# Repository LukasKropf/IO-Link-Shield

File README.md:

# IO-Link-Shield

Das IO-Link-Shield für Arduino wurde an der BFH  im Rahmen einer Projektarbeit erarbeitet. 
Dieses Repository enthällt alle wichtigen Daten zum Projekt. 

Die Dokumentation ist im Ordner Dokumente zu finden

[Bericht_io-Link Shield](https://github.com/LukasKropf/IO-Link-Shield/blob/master/Dokumente/Bericht_IO-Link%20Shield.pdf)

# Weiterführende Arbeiten:

Einige Zeit später wurde ein Nachfolgeprojekt gestartet in Rahmen einer Bachelorthesis.

[IO-Link Master Shield/Hat für Arduino und Raspberry Pi](https://bfh.easydocmaker.ch/search/abstract/2056/)

https://github.com/openiolink/io-link-master-shield-hat-sw

# Bilder

Hier einige Renderings:

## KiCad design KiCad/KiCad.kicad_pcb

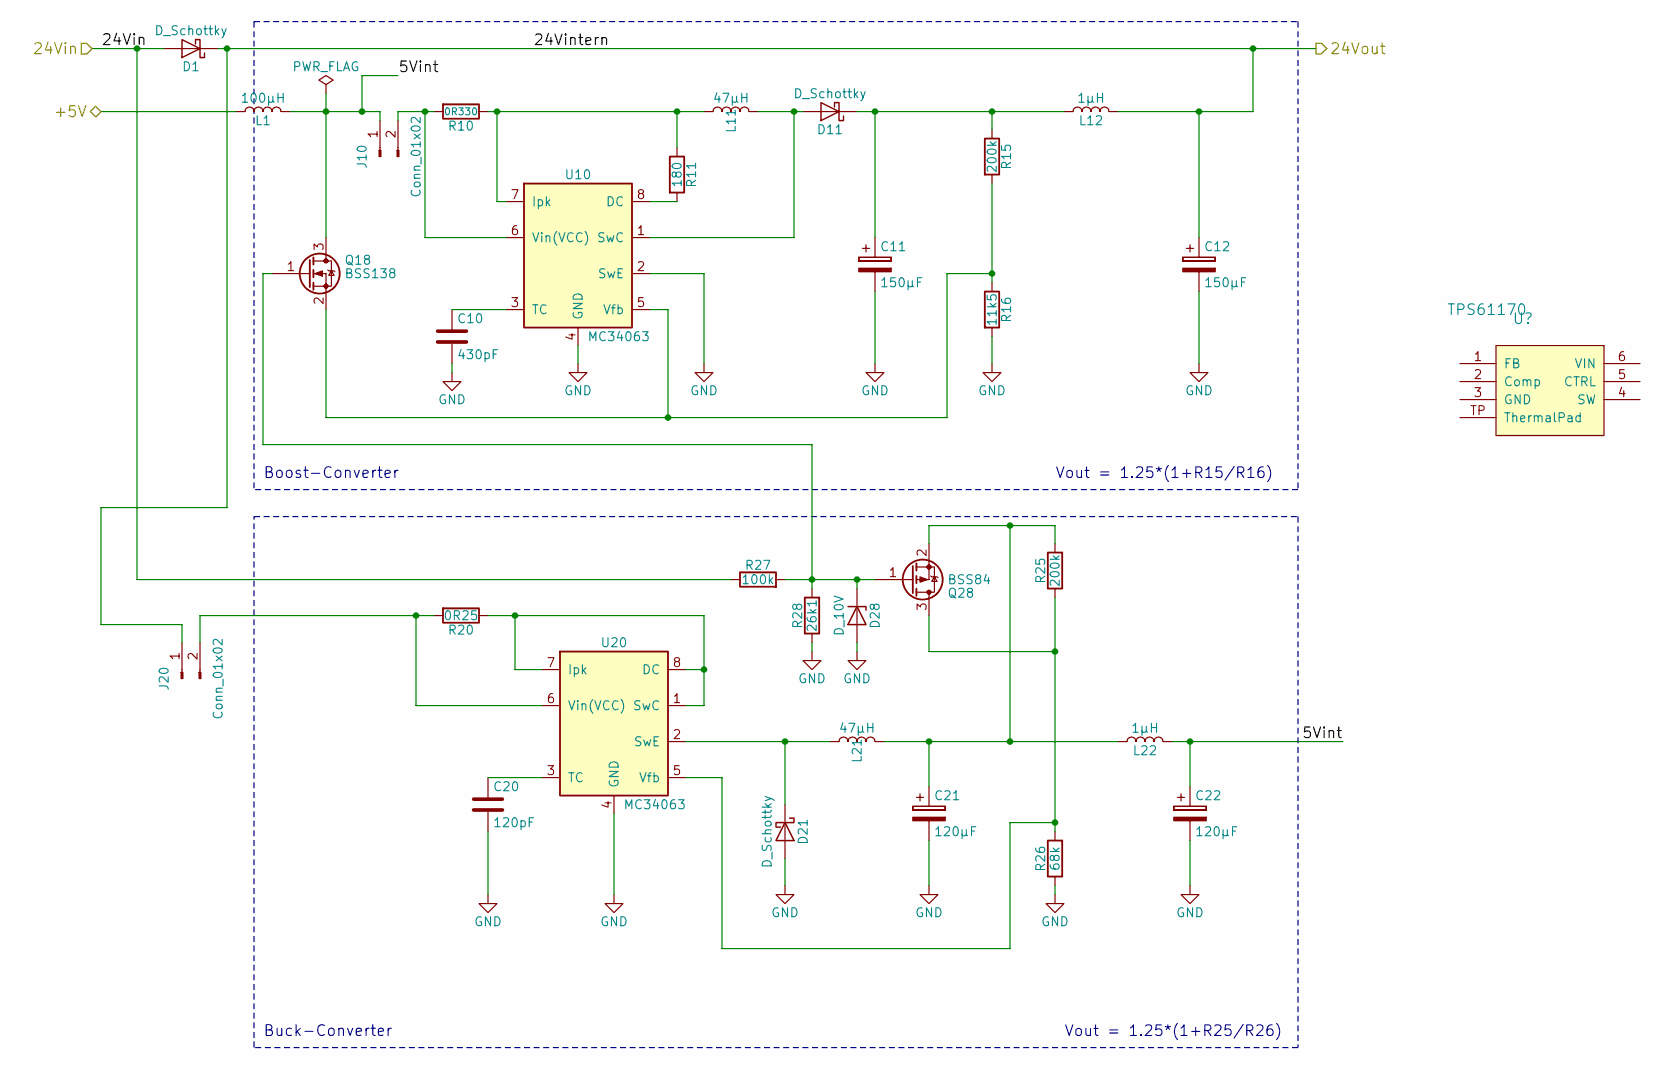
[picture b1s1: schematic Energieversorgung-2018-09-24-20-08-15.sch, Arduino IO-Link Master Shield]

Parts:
C10: 430pF; C_0805; part-num C0805C431J5GAC7800
C11, C12: 150µF; CP_Elec_8x10.5; part-num 35PEV150M8X10.5
C20: 120pF; C_0805; part-num GRM2165C1H121JA01D
C21, C22: 120µF; CP_Elec_6.3x5.7; part-num RSA1A121MCN1GS
D1, D11, D21: D_Schottky; D_SMF_DO-219; part-num SL04-HE3-08
D28: D_10V; D_SOD-123F; part-num NZH10C115
J10, J20: Conn_01x02; Pin_Header_Straight_1x02_Pitch2.54mm; part-num S1011EC-02-ND;SPC02SYAN
L1: 100µH; Murata_DG8040C; part-num 1267AY-101M=P3
L11, L21: 47µH; SRN6045; part-num SRN6045-470M
L12, L22: 1µH; L_0805; part-num LQM21FN1R0N00D
Q18: BSS138; SOT-23; part-num BSS138TA
Q28: BSS84; SOT-23; part-num BSS84-7-F
R10: 0R330; R_0805; part-num RL0805FR-7W0R33L
R11: 180; R_0805; part-num RC0805FR-07180RL
R15, R25: 200k; R_0805; part-num RC0805FR-07200KL
R16: 11k5; R_0805; part-num RC0805FR-0711K5L
R20: 0R25; R_0805; part-num RL0805FR-070R25L
R26: 68k; R_0805; part-num RC0805FR-0768KL
R27: 100k; R_0805; part-num RC0805FR-07100KL
R28: 26k1; R_0805; part-num RC0805FR-0726K1L
U10, U20: MC34063; SOIC-8-N; part-num MC34063ACD-TR

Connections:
/5V: L1.1; also elsewhere on the board
/24V: C12.1, D1.1 (K), J20.1, L12.2; also elsewhere on the board
/Energieversorgung/5Vint: C22.1, J10.1, L1.2, L22.2, Q18.3 (D)
/Energieversorgung/24Vin: D1.2 (A), R27.1; also elsewhere on the board
GND: C10.2, C11.2, C12.2, C20.2, C21.2, C22.2, D21.2 (A), D28.2 (A), R16.2, R26.1, R28.1, U10.2 (SwE), U10.4 (GND), U20.4 (GND); also elsewhere on the board
unnamed: C10.1, U10.3 (TC)
unnamed: C11.1, D11.1 (K), L12.1, R15.1
unnamed: C20.1, U20.3 (TC)
unnamed: C21.1, L21.2, L22.1, Q28.2 (S), R25.2
unnamed: D11.2 (A), L11.2, U10.1 (SwC)
unnamed: D21.1 (K), L21.1, U20.2 (SwE)
unnamed: D28.1 (K), Q18.1 (G), Q28.1 (G), R27.2, R28.2
unnamed: J10.2, R10.2, U10.6 (Vin(VCC))
unnamed: J20.2, R20.2, U20.6 (Vin(VCC))
unnamed: L11.1, R10.1, R11.1, U10.7 (Ipk)
unnamed: Q18.2 (S), R15.2, R16.1, U10.5 (Vfb)
unnamed: Q28.3 (D), R25.1, R26.2, U20.5 (Vfb)
unnamed: R11.2, U10.8 (DC)
unnamed: R20.1, U20.1 (SwC), U20.7 (Ipk), U20.8 (DC)

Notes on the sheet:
Boost-Converter
Buck-Converter
Vout = 1.25*(1+R15/R16)
Vout = 1.25*(1+R25/R26)

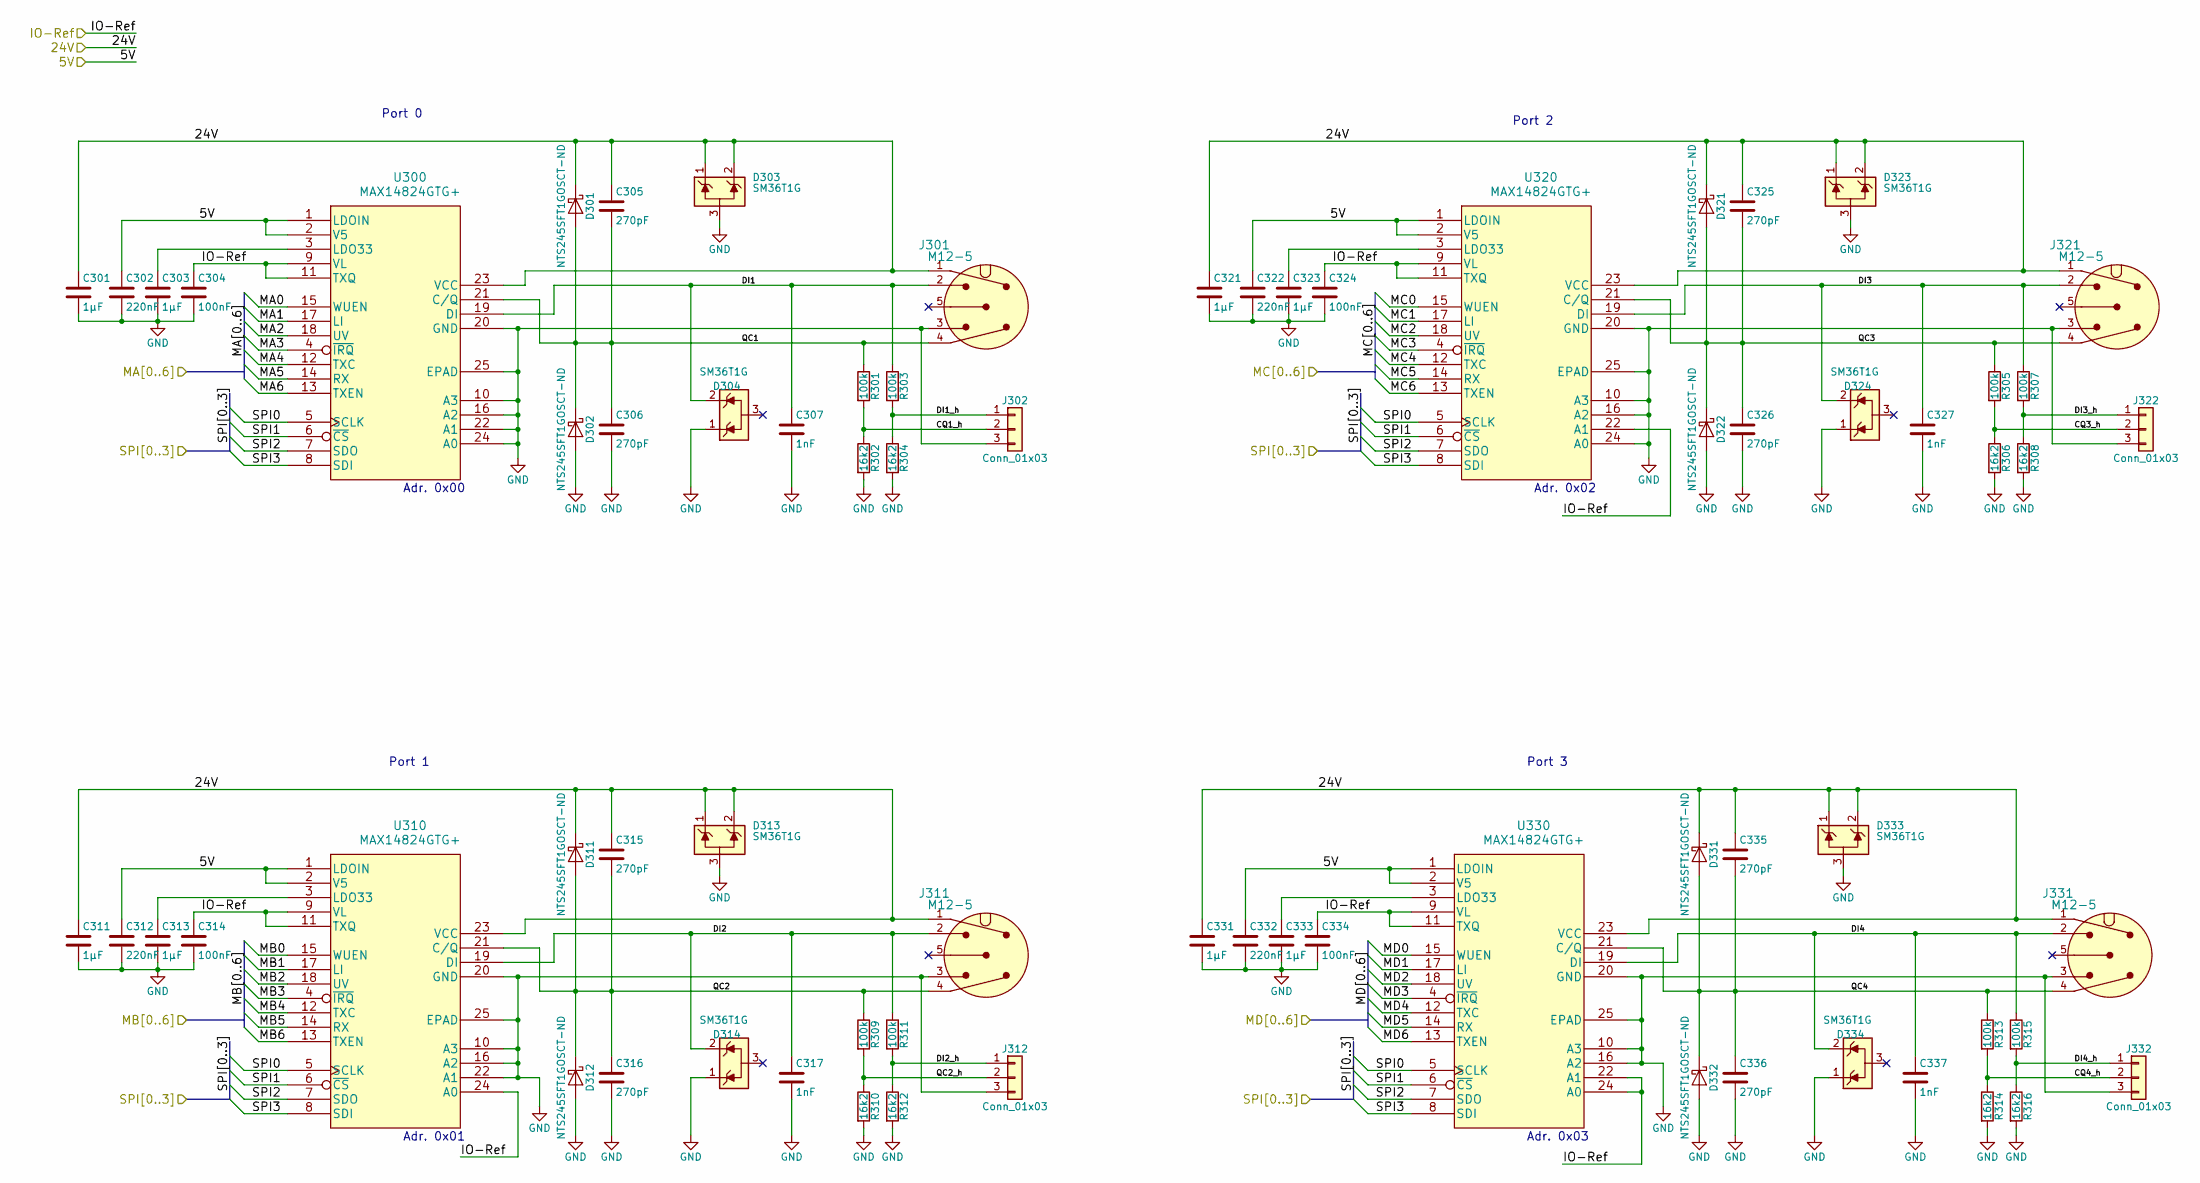
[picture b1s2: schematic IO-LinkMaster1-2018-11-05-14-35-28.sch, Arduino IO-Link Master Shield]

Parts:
C301, C311, C321, C331: 1µF; C_0805; part-num 885012207103
C302, C312, C322, C332: 220nF; C_0805; part-num 885012207018
C303, C313, C323, C333: 1µF; C_0805; part-num 885012207022
C304, C314, C324, C334: 100nF; C_0805; part-num 885012207016
C305, C306, C315, C316, C325, C326, C335, C336: 270pF; C_0805; part-num GRM2165C1H271JA01D
C307, C317, C327, C337: 1nF; C_0805; part-num GRM216R71H102KA01D
D301, D302, D311, D312, D321, D322, D331, D332: NTS245SFT1GOSCT-ND; D_SOD-123F; part-num NTS245SFT1GOSCT-ND
D303, D304, D313, D314, D323, D324, D333, D334: SM36T1G; SOT-23; part-num SM36T1G
J301, J311, J321, J331: M12-5; Phoenix_SACC-DSIV-M12FS-5CON-L180; part-num 1694237
J302, J312, J322, J332: Conn_01x03; Socket_Strip_Straight_1x03_Pitch2.54mm; part-num PPPC031LFBN-RC
R301, R303, R305, R307, R309, R311, R313, R315: 100k; R_0805; part-num RC0805FR-07100KL
R302, R304, R306, R308, R310, R312, R314, R316: 16k2; R_0805; part-num RC0805FR-0716K2L
U300, U310, U320, U330: MAX14824GTG+; QFN-24-1EP_4x4mm_Pitch0.5mm_Maxim; part-num MAX14824GTG+

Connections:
/0(Rx0): U300.14 (RX); also elsewhere on the board
/1(Tx0): U300.12 (TXC); also elsewhere on the board
/2(**): U330.4 (~IRQ); also elsewhere on the board
/3(**): U320.4 (~IRQ); also elsewhere on the board
/4(**): U310.4 (~IRQ); also elsewhere on the board
/5(**): U300.4 (~IRQ); also elsewhere on the board
/5V: C302.1, C312.1, C322.1, C332.1, U300.1 (LDOIN), U300.2 (V5), U310.1 (LDOIN), U310.2 (V5), U320.1 (LDOIN), U320.2 (V5), U330.1 (LDOIN), U330.2 (V5); also elsewhere on the board
/6(**): U300.13 (TXEN); also elsewhere on the board
/7(**): U300.18 (UV); also elsewhere on the board
/8(**): U300.17 (LI); also elsewhere on the board
/9(**): U300.15 (WUEN); also elsewhere on the board
/10(**): U300.6 (~CS), U310.6 (~CS), U320.6 (~CS), U330.6 (~CS); also elsewhere on the board
/14(Tx3): U330.12 (TXC); also elsewhere on the board
/15(Rx3): U330.14 (RX); also elsewhere on the board
/16(Tx2): U320.12 (TXC); also elsewhere on the board
/17(Rx2): U320.14 (RX); also elsewhere on the board
/18(Tx1): U310.12 (TXC); also elsewhere on the board
/19(Rx1): U310.14 (RX); also elsewhere on the board
/22: U330.15 (WUEN); also elsewhere on the board
/23: U330.17 (LI); also elsewhere on the board
/24: U330.18 (UV); also elsewhere on the board
/24V: C301.1, C305.1, C311.1, C315.1, C321.1, C325.1, C331.1, C335.1, D301.1 (K), D303.1 (K), D303.2 (K), D311.1 (K), D313.1 (K), D313.2 (K), D321.1 (K), D323.1 (K), D323.2 (K), D331.1 (K), D333.1 (K), D333.2 (K), J301.1, J311.1, J321.1, J331.1, U300.23 (VCC), U310.23 (VCC), U320.23 (VCC), U330.23 (VCC); also elsewhere on the board
/25: U330.13 (TXEN); also elsewhere on the board
/26: U320.15 (WUEN); also elsewhere on the board
/27: U320.17 (LI); also elsewhere on the board
/28: U320.18 (UV); also elsewhere on the board
/29: U320.13 (TXEN); also elsewhere on the board
/30: U310.15 (WUEN); also elsewhere on the board
/31: U310.17 (LI); also elsewhere on the board
/32: U310.18 (UV); also elsewhere on the board
/33: U310.13 (TXEN); also elsewhere on the board
/50: U300.7 (SDO), U310.7 (SDO), U320.7 (SDO), U330.7 (SDO); also elsewhere on the board
/52: U300.5 (SCLK), U310.5 (SCLK), U320.5 (SCLK), U330.5 (SCLK); also elsewhere on the board
/53: U300.8 (SDI), U310.8 (SDI), U320.8 (SDI), U330.8 (SDI); also elsewhere on the board
/IO-LinkMaster1/CQ1_h: J302.2, R301.2, R302.1
/IO-LinkMaster1/CQ3_h: J322.2, R305.2, R306.1
/IO-LinkMaster1/CQ4_h: J332.2, R313.2, R314.1
/IO-LinkMaster1/DI1: C307.1, D304.2 (K), J301.2, R303.1, U300.19 (DI)
/IO-LinkMaster1/DI1_h: J302.1, R303.2, R304.1
/IO-LinkMaster1/DI2: C317.1, D314.2 (K), J311.2, R311.1, U310.19 (DI)
/IO-LinkMaster1/DI2_h: J312.1, R311.2, R312.1
/IO-LinkMaster1/DI3: C327.1, D324.2 (K), J321.2, R307.1, U320.19 (DI)
/IO-LinkMaster1/DI3_h: J322.1, R307.2, R308.1
/IO-LinkMaster1/DI4: C337.1, D334.2 (K), J331.2, R315.1, U330.19 (DI)
/IO-LinkMaster1/DI4_h: J332.1, R315.2, R316.1
/IO-LinkMaster1/QC1: C305.2, C306.1, D301.2 (A), D302.1 (K), J301.4, R301.1, U300.21 (C/Q)
/IO-LinkMaster1/QC2: C315.2, C316.1, D311.2 (A), D312.1 (K), J311.4, R309.1, U310.21 (C/Q)
/IO-LinkMaster1/QC2_h: J312.2, R309.2, R310.1
/IO-LinkMaster1/QC3: C325.2, C326.1, D321.2 (A), D322.1 (K), J321.4, R305.1, U320.21 (C/Q)
/IO-LinkMaster1/QC4: C335.2, C336.1, D331.2 (A), D332.1 (K), J331.4, R313.1, U330.21 (C/Q)
/IO-Ref: C304.1, C314.1, C324.1, C334.1, U300.9 (VL), U300.11 (TXQ), U310.9 (VL), U310.11 (TXQ), U310.24 (A0), U320.9 (VL), U320.11 (TXQ), U320.22 (A1), U330.9 (VL), U330.11 (TXQ), U330.22 (A1), U330.24 (A0); also elsewhere on the board
GND: C301.2, C302.2, C303.2, C304.2, C306.2, C307.2, C311.2, C312.2, C313.2, C314.2, C316.2, C317.2, C321.2, C322.2, C323.2, C324.2, C326.2, C327.2, C331.2, C332.2, C333.2, C334.2, C336.2, C337.2, D302.2 (A), D303.3 (A), D304.1 (K), D312.2 (A), D313.3 (A), D314.1 (K), D322.2 (A), D323.3 (A), D324.1 (K), D332.2 (A), D333.3 (A), D334.1 (K), J301.3, J302.3, J311.3, J312.3, J321.3, J322.3, J331.3, J332.3, R302.2, R304.2, R306.2, R308.2, R310.2, R312.2, R314.2, R316.2, U300.10 (A3), U300.16 (A2), U300.20 (GND), U300.22 (A1), U300.24 (A0), U300.25 (EPAD), U310.10 (A3), U310.16 (A2), U310.20 (GND), U310.22 (A1), U310.25 (EPAD), U320.10 (A3), U320.16 (A2), U320.20 (GND), U320.24 (A0), U320.25 (EPAD), U330.10 (A3), U330.16 (A2), U330.20 (GND), U330.25 (EPAD); also elsewhere on the board
unnamed: C303.1, U300.3 (LDO33)
unnamed: C313.1, U310.3 (LDO33)
unnamed: C323.1, U320.3 (LDO33)
unnamed: C333.1, U330.3 (LDO33)

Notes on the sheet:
Adr. 0x00
Adr. 0x02
Adr. 0x01
Adr. 0x03
Port 1
Port 0
Port 2
Port 3

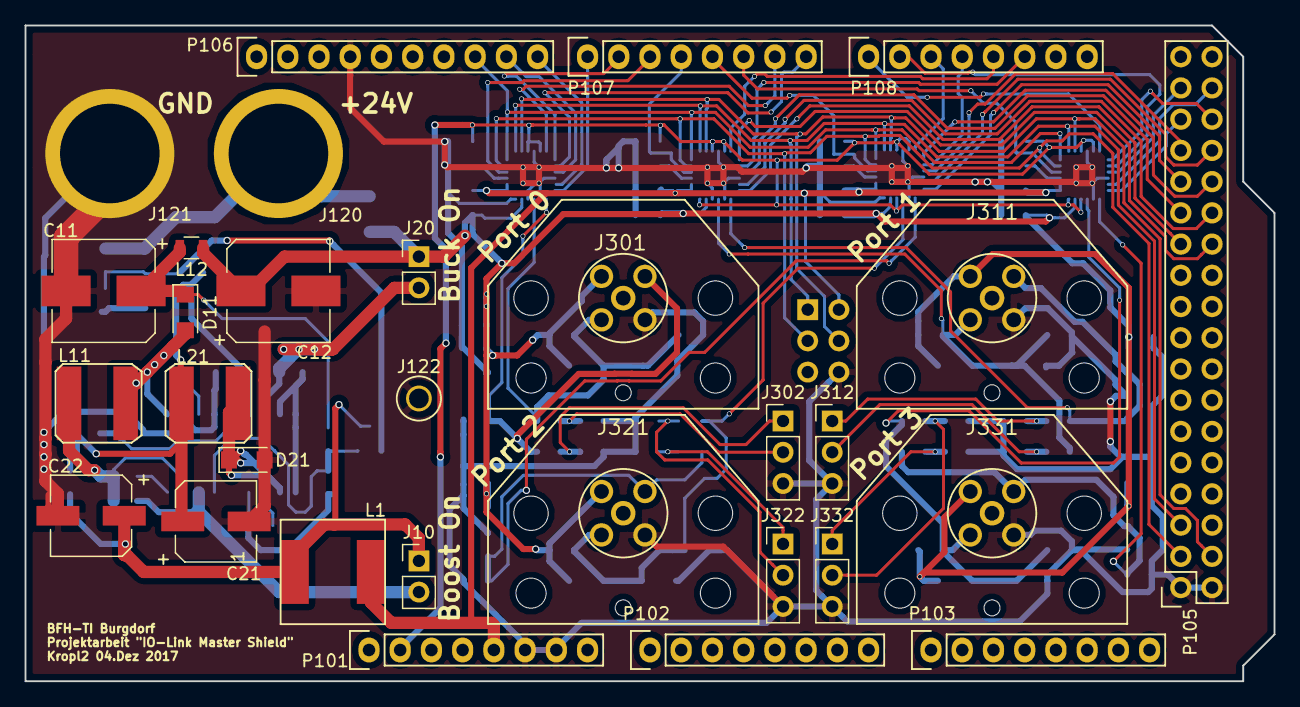
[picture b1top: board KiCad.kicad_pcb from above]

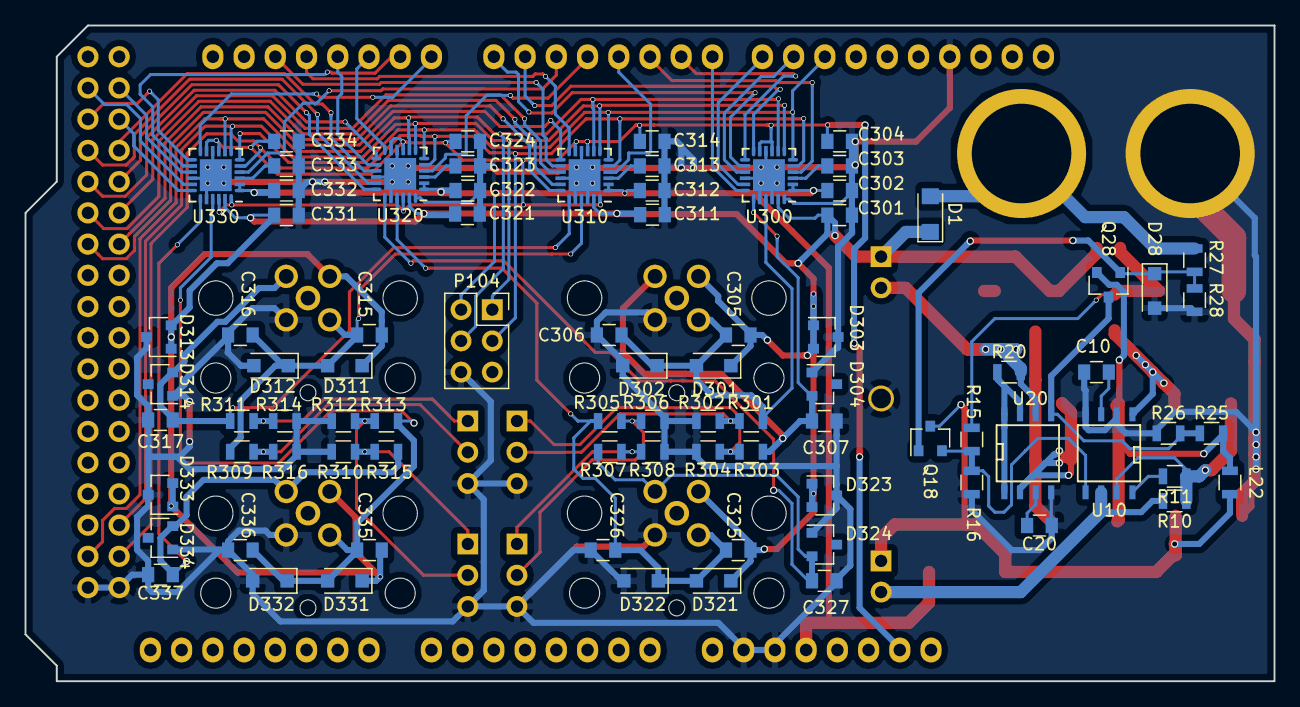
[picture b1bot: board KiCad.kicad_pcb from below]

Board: 2 copper layers, 101.6 x 53.3 mm, 113 parts (83 on the bottom side), 72 nets.

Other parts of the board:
J120, J121: MDm Banana; Banana_4mm_CT2230
J122: TEST_1P; TestPoint_Keystone_5006_Black
P101: Power; Socket_Strip_Arduino_1x08
P102, P103: Analog; Socket_Strip_Arduino_1x08
P104: SPI; Socket_Strip_Straight_2x03_Pitch2.54mm
P105: Digital; Socket_Strip_Arduino_2x18
P106: PWM; Socket_Strip_Arduino_1x10
P107: PWM; Socket_Strip_Arduino_1x08
P108: Communication; Socket_Strip_Arduino_1x08

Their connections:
/0(Rx0): P107.8; also elsewhere on the board
/1(Tx0): P107.7; also elsewhere on the board
/2(**): P107.6; also elsewhere on the board
/3(**): P107.5; also elsewhere on the board
/4(**): P107.4; also elsewhere on the board
/5(**): P107.3; also elsewhere on the board
/5V: P101.5, P104.2; also elsewhere on the board
/6(**): P107.2; also elsewhere on the board
/7(**): P107.1; also elsewhere on the board
/8(**): P106.10; also elsewhere on the board
/9(**): P106.9; also elsewhere on the board
/10(**): P106.8; also elsewhere on the board
/14(Tx3): P108.1; also elsewhere on the board
/15(Rx3): P108.2; also elsewhere on the board
/16(Tx2): P108.3; also elsewhere on the board
/17(Rx2): P108.4; also elsewhere on the board
/18(Tx1): P108.5; also elsewhere on the board
/19(Rx1): P108.6; also elsewhere on the board
/22: P105.33; also elsewhere on the board
/23: P105.34; also elsewhere on the board
/24: P105.31; also elsewhere on the board
/25: P105.32; also elsewhere on the board
/26: P105.29; also elsewhere on the board
/27: P105.30; also elsewhere on the board
/28: P105.27; also elsewhere on the board
/29: P105.28; also elsewhere on the board
/30: P105.25; also elsewhere on the board
/31: P105.26; also elsewhere on the board
/32: P105.23; also elsewhere on the board
/33: P105.24; also elsewhere on the board
/50: P104.1, P105.5; also elsewhere on the board
/52: P104.3, P105.3; also elsewhere on the board
/53: P104.4, P105.4; also elsewhere on the board
/Energieversorgung/24Vin: J120.1; also elsewhere on the board
/IO-Ref: P101.2; also elsewhere on the board
GND: J121.1, J122.1, P101.6, P101.7, P104.6, P105.1, P105.2, P106.4; also elsewhere on the board

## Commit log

2020-10-06 First Commit
    Alle wichtigen Daten werden hier hochgeladen.
2020-10-06 Beschreibung erweitert
